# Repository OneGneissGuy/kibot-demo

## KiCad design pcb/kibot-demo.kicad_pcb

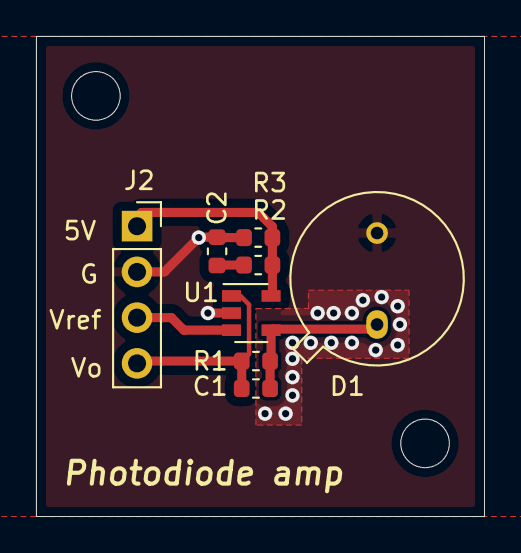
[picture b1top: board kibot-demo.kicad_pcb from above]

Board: 2 copper layers, 24.9 x 26.7 mm, 10 parts (0 on the bottom side), 6 nets.

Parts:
C1: 3.3pF; C_0603_1608Metric
C2: 1uF; C_0603_1608Metric
D1: BPX61; TO-5-2_Window
H1, H2: MountingHole; MountingHole_2.7mm_M2.5
J2: Conn_01x04; PinSocket_1x04_P2.54mm_Vertical
R1: 2M; R_0603_1608Metric
R2: 13.7K; R_0603_1608Metric
R3: 280R; R_0603_1608Metric
U1: OPA333xxDBV; SOT-23-5

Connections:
+5V: J2.1, R2.2, R3.2, U1.5
/Vout: C1.2, J2.4, R1.2, U1.1
/Vref: J2.3, U1.3
GND: C2.1, D1.2, J2.2, R3.1, U1.2
unnamed: C1.1, D1.1, R1.1, U1.4
unnamed: C2.2, R2.1

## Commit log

2022-03-22 create pcb
